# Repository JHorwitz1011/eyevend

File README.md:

# eyevend
Adapting vending machines for the blind and low vision community

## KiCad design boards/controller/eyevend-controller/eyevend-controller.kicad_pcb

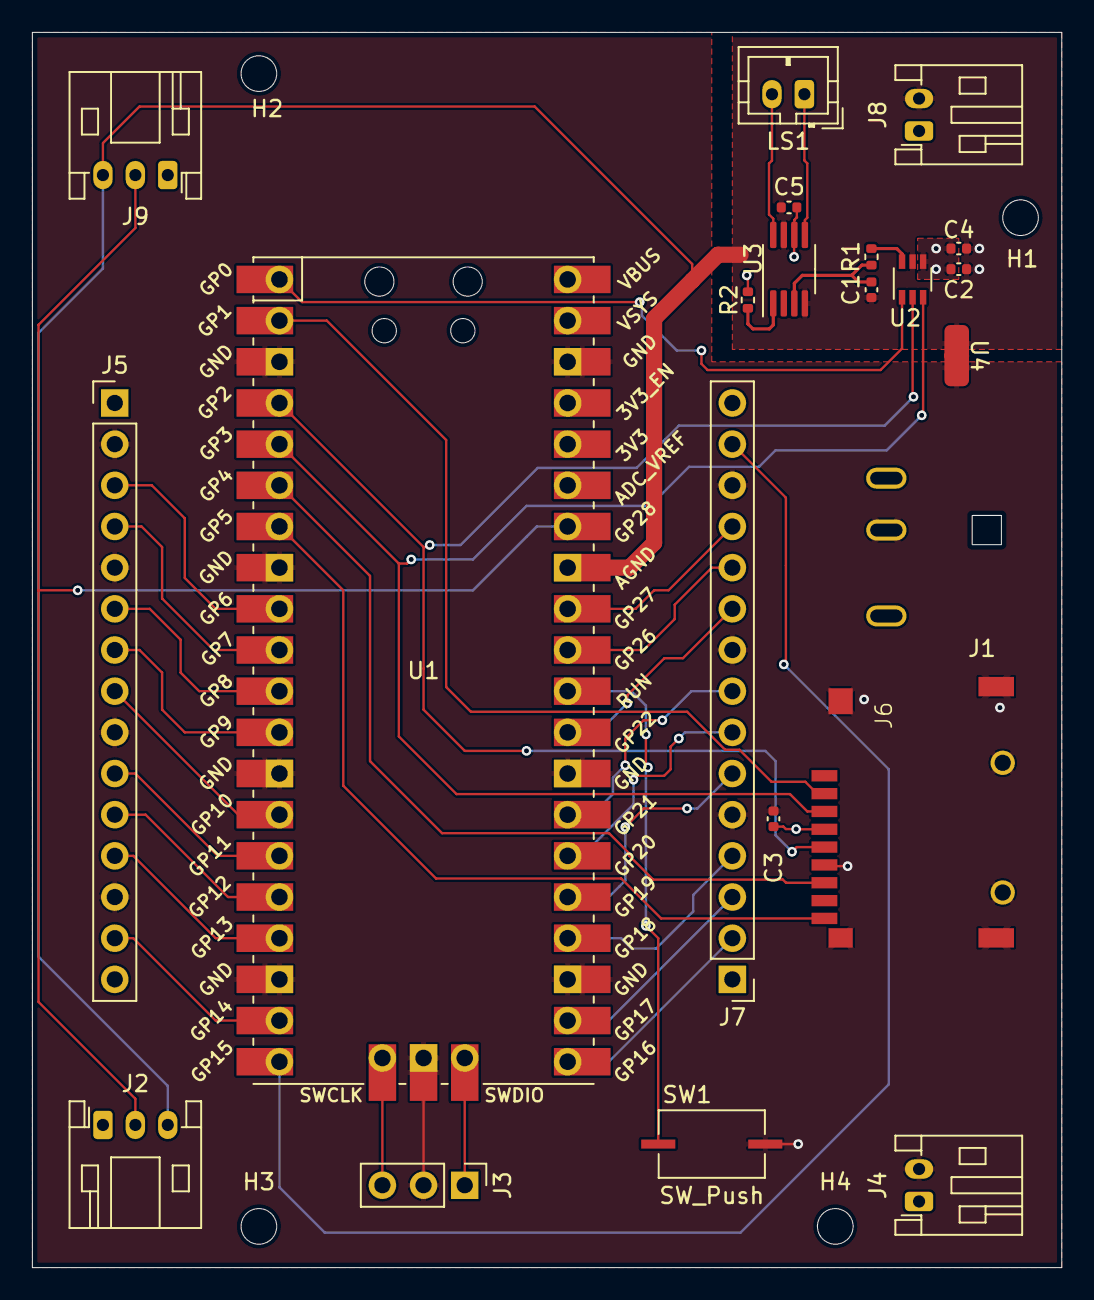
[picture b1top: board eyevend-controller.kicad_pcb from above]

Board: 4 copper layers, 63.5 x 76.2 mm, 26 parts (0 on the bottom side), 38 nets.

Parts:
C1: 10n; C_0402_1005Metric
C2, C3: 0.1u; C_0402_1005Metric
C4, C5: 1u; C_0402_1005Metric
H1, H2, H3, H4: MountingHole_Pad; MountingHole_2.2mm_M2_ISO7380
J1: Barrel_Jack_Switch; DC-0440-2.5A-2.5
J2, J9: sig; JST_PH_S3B-PH-K_1x03_P2.00mm_Horizontal
J3: swd; PinHeader_1x03_P2.54mm_Vertical
J4: pwr_utilL; JST_PH_S2B-PH-K_1x02_P2.00mm_Horizontal
J5, J7: Conn_01x15; PinHeader_1x15_P2.54mm_Vertical
J6: Micro_SD_Card_Det1; GT-TF003-H0185-02
J8: pwr_utilR; JST_PH_S2B-PH-K_1x02_P2.00mm_Horizontal
LS1: Speaker; JST_PH_B2B-PH-K_1x02_P2.00mm_Vertical
R1, R2: 10k; R_0402_1005Metric
SW1: SW_Push; PTS636 6.0x3.5 Button
U1: Pico; RPi_Pico_SMD_TH
U2: DAC8411; Texas_R-PDSO-G6
U3: PAM8302AAD; MSOP-8_3x3mm_P0.65mm
U4: GND_STARPOINT; gndstarpoint

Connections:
+3.3V: C2.1, C3.1, C4.1, C5.1, J2.1, J5.1, J5.15, J6.4 (VDD), J7.1, J7.15, J9.1, R2.2, U1.36 (3V3), U2.4 (VDDA), U3.6 (VDD)
+5V: J1.1, J4.1, J8.1, U1.39 (VSYS)
/DAC_CS: U1.1 (GPIO0), U2.1 (SYNC)
/GP6: J5.3, U1.9 (GPIO6)
/GP7: J5.4, U1.10 (GPIO7)
/GP8: J5.6, U1.11 (GPIO8)
/GP9: J5.7, U1.12 (GPIO9)
/GP10: J5.8, U1.14 (GPIO10)
/GP11: J5.10, U1.15 (GPIO11)
/GP12: J5.11, U1.16 (GPIO12)
/GP13: J5.12, U1.17 (GPIO13)
/GP14: J5.14, U1.19 (GPIO14)
/GP15: J7.14, U1.20 (GPIO15)
/GP16: J7.2, U1.21 (GPIO16)
/GP17: J7.3, U1.22 (GPIO17)
/GP18: J7.4, U1.24 (GPIO18)
/GP19: J7.6, U1.25 (GPIO19)
/GP20: J7.7, U1.26 (GPIO20)
/GP21: J7.8, U1.27 (GPIO21)
/GP22: J7.10, U1.29 (GPIO22)
/GP26: J7.11, U1.31 (GPIO26_ADC0)
/GP27: J7.12, U1.32 (GPIO27_ADC1)
/SD_CD: J6.9 (DET), U1.7 (GPIO5)
/SIG: J2.2, J9.2, U1.34 (GPIO28_ADC2)
/SPI_CIPO: J6.7 (DAT0), U1.6 (GPIO4)
/SPI_CLK: J6.5 (CLK), U1.4 (GPIO2), U2.2 (SCK)
/SPI_COPI: J6.3 (CMD), U1.5 (GPIO3), U2.3 (DIN)
/SWCLK: J3.3, U1.41 (SWCLK)
/SWDIO: J3.1, U1.43 (SWDIO)
/mSD_CS: J6.2 (DAT3/CD), U1.2 (GPIO1)
GND: C3.2, J1.2, J3.2, J4.2, J5.2, J5.5, J5.9, J5.13, J6.6 (VSS), J6.10 (SHIELD), J7.5, J7.9, J7.13, SW1.2, U1.3 (GND), U1.8 (GND), U1.13 (GND), U1.18 (GND), U1.23 (GND), U1.28 (GND), U1.38 (GND), U1.42 (GND), U4.2 (gnd)
GNDA: C1.2, C2.2, C4.2, C5.2, J2.3, J8.2, J9.3, U1.33 (AGND), U2.5 (GND), U3.4 (IN-), U3.7 (GND), U4.1 (gnda)
unnamed: SW1.1, U1.30 (RUN)
unnamed: R1.2, U2.6 (VOUT)
unnamed: C1.1, R1.1, U3.3 (IN+)
unnamed: LS1.1, U3.5 (OUT+)
unnamed: LS1.2, U3.8 (OUT-)
unnamed: R2.1, U3.1 (~SD)

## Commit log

2023-12-18 models updated
2023-12-28 updated board
2023-12-28 Footprint of microsd card
2024-01-17 board finished, need to order still
2024-01-17 added mounting holes
